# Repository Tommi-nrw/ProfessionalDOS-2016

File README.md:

Professional DOS was the fastest floppy speeder (excluding RAM disk setups)
for the Commodore 64 / 128 and 1541 / 1571 back in the '80s.
It was sold as RapiDOS in the US and DISK DEMON in the UK.

This is an upgraded version of the rebuilt Professional DOS from 2016.

The PCB works with both the 1541 and 1571. 
In the 1541, the board also lets you switch between Professional DOS, SpeedDOS, and DolphinDOS.

Version 1.42 (2026) eliminates the need for jumper wires.

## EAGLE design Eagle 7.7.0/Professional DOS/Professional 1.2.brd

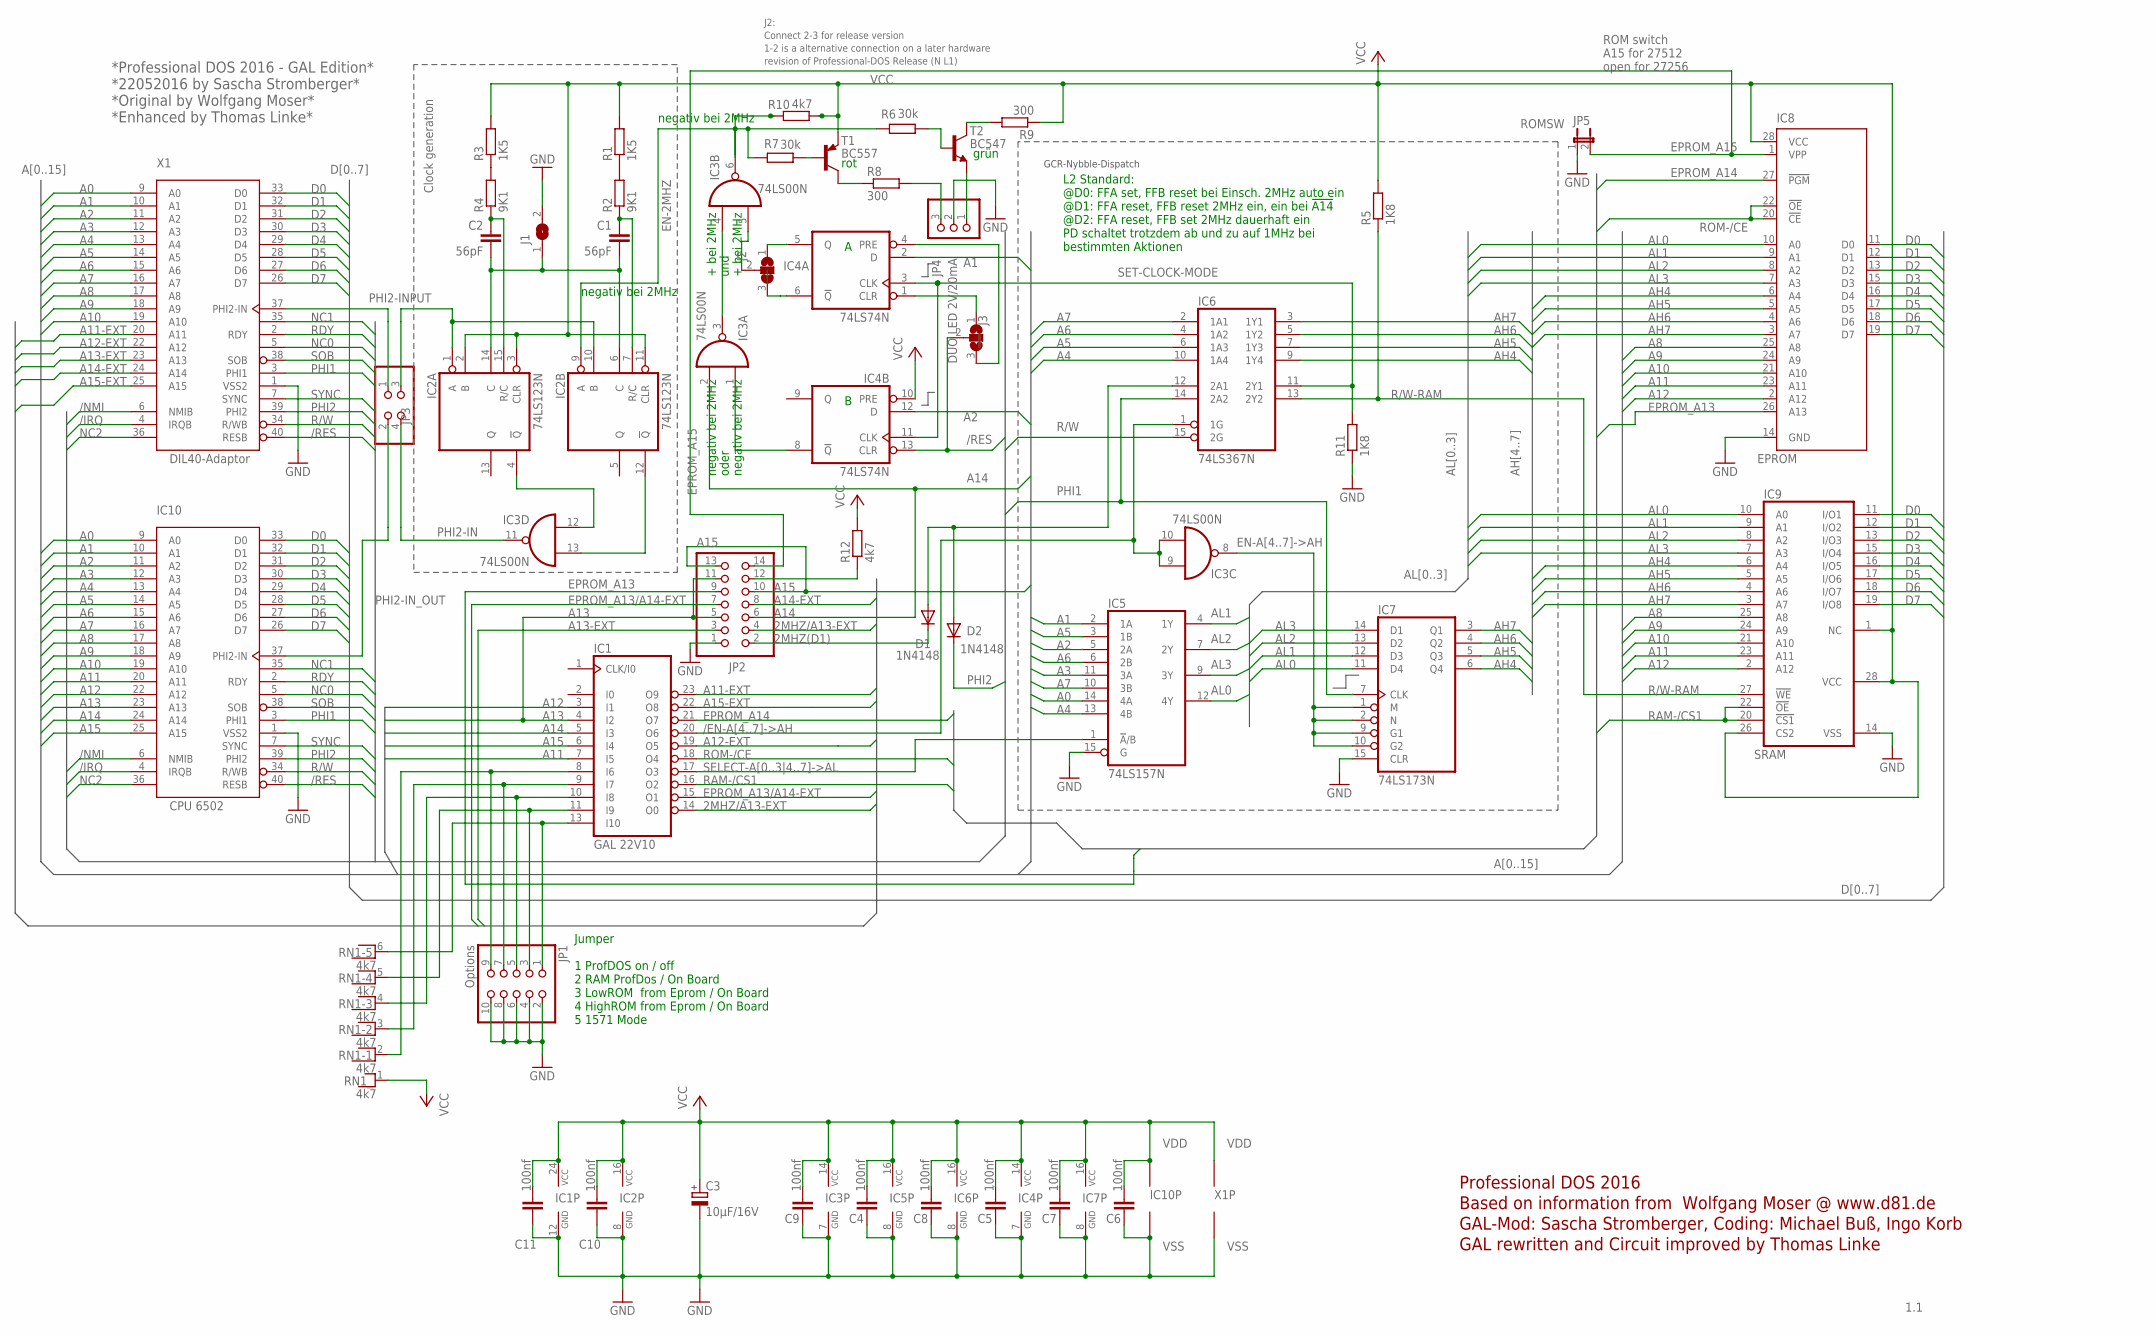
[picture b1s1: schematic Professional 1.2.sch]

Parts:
C1, C2: 56pF; C025-025X050
C3: 10µF/16V; TT2D4
C4, C5, C6, C7, C8, C9, C10, C11: 100nf; C2.5-2
D1, D2: 1N4148; D-5
IC1: GAL 22V10; DIL24-3
IC2: 74LS123N; DIL16
IC3: 74LS00N; DIL14
IC4: 74LS74N; DIL14
IC5: 74LS157N; DIL16
IC6: 74LS367N; DIL16
IC7: 74LS173N; DIL16
IC8: EPROM; DIL28-6
IC9: SRAM; DIL28-6
IC10: CPU 6502; DIL40
J1: 1; SJ
J2, J3: Alternativ connection for old version; SJ_2
JP1: Options; 2X05
JP2: 1; 2X07
JP3: 1; 2X02
JP4: DUO LED 2V/20mA; 1X03
JP5: ROMSW; JP1
R1, R3: 1K5; 0207/2V
R2, R4: 9K1; 0207/2V
R5, R11: 1K8; 0207/7
R6, R7: 30k; 0207/2V
R8, R9: 300; 0207/2V
R10: 4k7; 0207/2V
R12: 4k7; 0207/7
RN1: 4k7; RN-6
T1: BC557; TO92
T2: BC547; TO92
X1: DIL40-Adaptor; DIL40-BPLACE

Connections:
2MHZ(D1): D1.C, JP2.2
2MHZ/A13-EXT: IC1.14 (O0), JP2.4
/EN-A[4..7]->AH: IC1.20 (O6), IC3.9 (I0), IC3.10 (I1), IC6.1 (1G)
/IRQ: IC10.4 (IRQB), X1.4 (IRQB)
/NMI: IC10.6 (NMIB), X1.6 (NMIB)
/Q: IC4.6 (!Q), J2.3
/RES: IC4.13 (CLR), IC10.40 (RESB), J3.2, X1.40 (RESB)
A0: IC5.14 (4A), IC10.9 (A0), X1.9 (A0)
A1: IC4.2 (D), IC5.2 (1A), IC10.10 (A1), X1.10 (A1)
A2: IC4.12 (D), IC5.5 (2A), IC10.11 (A2), X1.11 (A2)
A3: IC5.11 (3A), IC10.12 (A3), X1.12 (A3)
A4: IC5.13 (4B), IC6.10 (1A4), IC10.13 (A4), X1.13 (A4)
A5: IC5.3 (1B), IC6.6 (1A3), IC10.14 (A5), X1.14 (A5)
A6: IC5.6 (2B), IC6.4 (1A2), IC10.15 (A6), X1.15 (A6)
A7: IC5.10 (3B), IC6.2 (1A1), IC10.16 (A7), X1.16 (A7)
A8: IC8.25 (A8), IC9.25 (A8), IC10.17 (A8), X1.17 (A8)
A9: IC8.24 (A9), IC9.24 (A9), IC10.18 (A9), X1.18 (A9)
A10: IC8.21 (A10), IC9.21 (A10), IC10.19 (A10), X1.19 (A10)
A11: IC1.7 (I5), IC8.23 (A11), IC9.23 (A11), IC10.20 (A11)
A11-EXT: IC1.23 (O9), X1.20 (A11)
A12: IC1.3 (I1), IC8.2 (A12), IC9.2 (A12), IC10.22 (A12)
A12-EXT: IC1.19 (O5), X1.22 (A12)
A13: IC1.4 (I2), IC10.23 (A13), JP2.5, JP2.11
A13-EXT: JP2.3, X1.23 (A13)
A14: IC1.5 (I3), IC3.2 (I1), IC10.24 (A14), JP2.6
A14-EXT: JP2.8, X1.24 (A14)
A15: IC1.6 (I4), IC10.25 (A15), JP2.10, JP2.13
A15-EXT: IC1.22 (O8), X1.25 (A15)
AH4: IC6.9 (1Y4), IC7.6 (Q4), IC8.6 (A4), IC9.6 (A4)
AH5: IC6.7 (1Y3), IC7.5 (Q3), IC8.5 (A5), IC9.5 (A5)
AH6: IC6.5 (1Y2), IC7.4 (Q2), IC8.4 (A6), IC9.4 (A6)
AH7: IC6.3 (1Y1), IC7.3 (Q1), IC8.3 (A7), IC9.3 (A7)
AL0: IC5.12 (4Y), IC7.11 (D4), IC8.10 (A0), IC9.10 (A0)
AL1: IC5.4 (1Y), IC7.12 (D3), IC8.9 (A1), IC9.9 (A1)
AL2: IC5.7 (2Y), IC7.13 (D2), IC8.8 (A2), IC9.8 (A2)
AL3: IC5.9 (3Y), IC7.14 (D1), IC8.7 (A3), IC9.7 (A3)
CLR: IC4.1 (CLR), J3.1
D0: IC8.11 (D0), IC9.11 (I/O1), IC10.33 (D0), X1.33 (D0)
D1: IC8.12 (D1), IC9.12 (I/O2), IC10.32 (D1), X1.32 (D1)
D2: IC8.13 (D2), IC9.13 (I/O3), IC10.31 (D2), X1.31 (D2)
D3: IC8.15 (D3), IC9.15 (I/O4), IC10.30 (D3), X1.30 (D3)
D4: IC8.16 (D4), IC9.16 (I/O5), IC10.29 (D4), X1.29 (D4)
D5: IC8.17 (D5), IC9.17 (I/O6), IC10.28 (D5), X1.28 (D5)
D6: IC8.18 (D6), IC9.18 (I/O7), IC10.27 (D6), X1.27 (D6)
D7: IC8.19 (D7), IC9.19 (I/O8), IC10.26 (D7), X1.26 (D7)
EN-2MHZ: IC2.9 (A), IC3.6 (O), R6.2, R7.1, R10.2
EN-A[4..7]->AH: IC3.8 (O), IC7.1 (M), IC7.2 (N), IC7.9 (G1), IC7.10 (G2)
EPROM_A13: IC8.26 (A13), JP2.9
EPROM_A13/A14-EXT: IC1.15 (O1), JP2.7
EPROM_A14: IC1.21 (O7), IC8.27 (!PGM)
EPROM_A15: IC8.1 (VPP), JP2.14, JP5.2
FETCH_CLOCK_MODE: D1.A, D2.A, IC6.12 (2A1)
GND: C3.-, C4.2, C5.2, C6.2, C7.2, C8.2, C9.2, C10.2, C11.2, IC1.12 (GND), IC2.8 (GND), IC3.7 (GND), IC4.7 (GND), IC5.8 (GND), IC5.15 (G), IC6.8 (GND), IC7.8 (GND), IC7.15 (CLR), IC8.14 (GND), IC9.14 (VSS), IC10.1 (VSS2), IC10.21 (VSS), J1.2, JP1.2, JP1.4, JP1.6, JP1.8, JP1.10, JP2.1, JP4.2, JP5.1, R11.1, X1.1 (VSS2), X1.21 (VSS)
unnamed: R3.1, R4.2
unnamed: C1.2, C2.2, IC2.6 (C), IC2.14 (C), J1.1
unnamed: C2.1, IC2.15 (R/C), R4.1
unnamed: C1.1, IC2.7 (R/C), R2.1
unnamed: R1.1, R2.2
unnamed: IC2.4 (!Q), IC3.12 (I0)
unnamed: R7.2, T1.2 (B)
unnamed: IC2.12 (!Q), IC3.13 (I1)
unnamed: IC3.5 (I1), J2.2
unnamed: R6.1, T2.2 (B)
unnamed: IC3.3 (O), IC3.4 (I0)
unnamed: IC3.1 (I0), IC4.8 (!Q)
unnamed: JP4.1, T2.1 (E)
unnamed: R9.2, T2.3 (C)
unnamed: JP4.3, R8.2
unnamed: R8.1, T1.3 (C)
NC0: IC10.5 (NC$3), X1.5 (NC$3)
NC1: IC10.35 (NC$1), X1.35 (NC$1)
NC2: IC10.36 (NC$2), X1.36 (NC$2)
ON-OFF: IC1.13 (I10), JP1.1, RN1.6
OPT2: IC1.11 (I9), JP1.3, RN1.5
OPT3: IC1.10 (I8), JP1.5, RN1.4
OPT4: IC1.9 (I7), JP1.7, RN1.3
OPT5: IC1.8 (I6), JP1.9, RN1.2
PHI1: IC6.14 (2A2), IC7.7 (CLK), IC10.3 (PHI1), X1.3 (PHI1)
PHI2: D2.C, IC10.39 (PHI2), X1.39 (PHI2)
PHI2-IN: IC3.11 (O), JP3.4
PHI2-INPUT: JP3.1, X1.37 (PHI2-IN)
PHI2-INPUT_OUT: IC2.1 (A), IC2.10 (B), JP3.3
PHI2-IN_OUT: IC10.37 (PHI2-IN), JP3.2
PRE: IC4.4 (PRE), J3.3
PULLUP: JP2.12, R12.1
Q: IC4.5 (Q), J2.1
R/W: IC6.15 (2G), IC10.34 (R/WB), X1.34 (R/WB)
R/W-RAM: IC6.13 (2Y2), IC9.27 (!WE), R5.1
RAM-/CS1: IC1.16 (O2), IC9.20 (!CS1), IC9.22 (!OE)
RDY: IC10.2 (RDY), X1.2 (RDY)
ROM-/CE: IC1.18 (O4), IC8.20 (!CE), IC8.22 (!OE)
SELECT-A[0..3|4..7]->AL: IC1.17 (O3), IC5.1 (!A!/B)
SET-CLOCK-MODE: IC4.3 (CLK), IC4.11 (CLK), IC6.11 (2Y1), R11.2
SOB: IC10.38 (SOB), X1.38 (SOB)
SYNC: IC10.7 (SYNC), X1.7 (SYNC)
VCC: C3.+, C4.1, C5.1, C6.1, C7.1, C8.1, C9.1, C10.1, C11.1, IC1.24 (VCC), IC2.2 (B), IC2.3 (CLR), IC2.11 (CLR), IC2.16 (VCC), IC3.14 (VCC), IC4.10 (PRE), IC4.14 (VCC), IC5.16 (VCC), IC6.16 (VCC), IC7.16 (VCC), IC8.28 (VCC), IC9.1 (NC), IC9.26 (CS2), IC9.28 (VCC), IC10.8 (VDD), R1.2, R3.2, R5.2, R9.1, R10.1, R12.2, RN1.1, T1.1 (E), X1.8 (VDD)

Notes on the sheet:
Clock generation
1.1
Professional DOS 2016 Based on information from Wolfgang Moser @ www.d81.de GAL-Mod: Sascha Stromberger, Coding: Michael Buß, Ingo Korb GAL rewritten and Circuit improved by Thomas Linke
*Professional DOS 2016 - GAL Edition* *22052016 by Sascha Stromberger* *Original by Wolfgang Moser* *Enhanced by Thomas Linke*
ROM switch A15 for 27512 open for 27256
1-2 is a alternative connection on a later hardware
revision of Professional-DOS Release (N L1)
GCR-Nybble-Dispatch
Connect 2-3 for release version
Jumper 1 ProfDOS on / off 2 RAM ProfDos / On Board 3 LowROM from Eprom / On Board 4 HighROM from Eprom / On Board 5 1571 Mode
rot
grün
J2:
L2 Standard: @D0: FFA set, FFB reset bei Einsch. 2MHz auto ein @D1: FFA reset, FFB reset 2MHz ein, ein bei !A14 @D2: FFA reset, FFB set 2MHz dauerhaft ein PD schaltet trotzdem ab und zu auf 1MHz bei bestimmten Aktionen
negativ bei 2MHz
+ bei 2MHz
oder
und

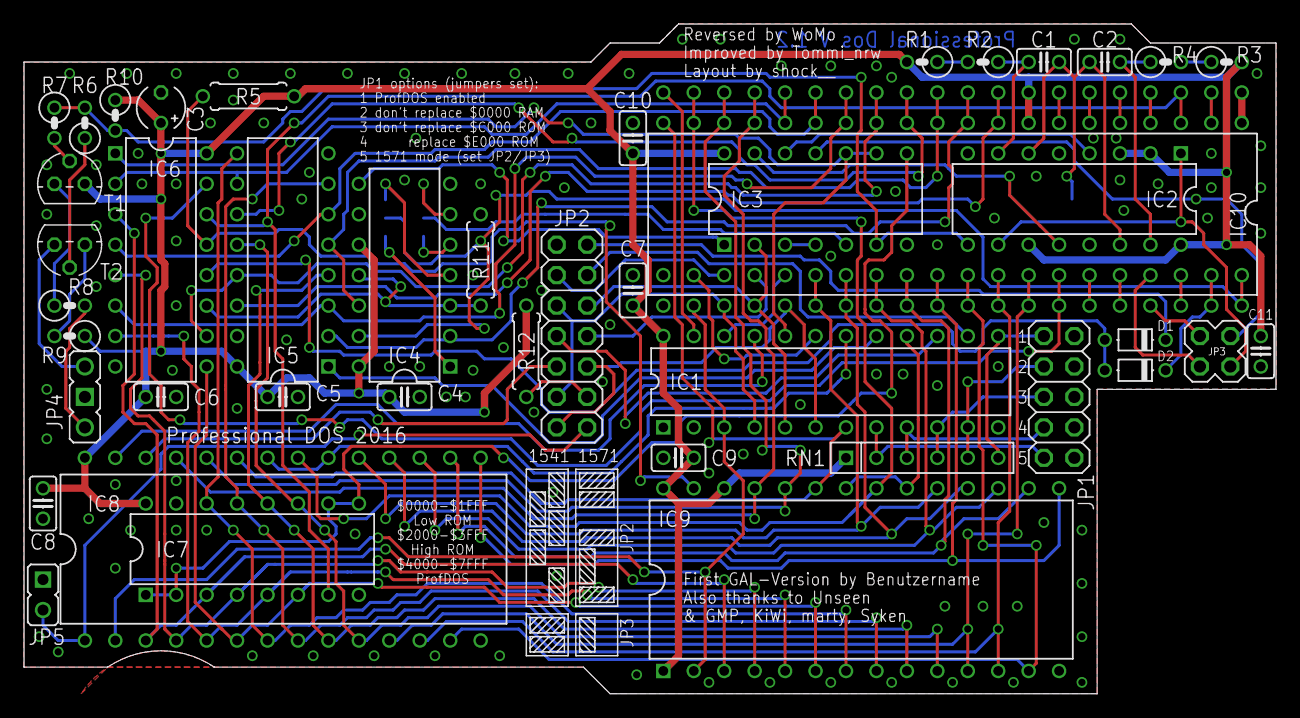
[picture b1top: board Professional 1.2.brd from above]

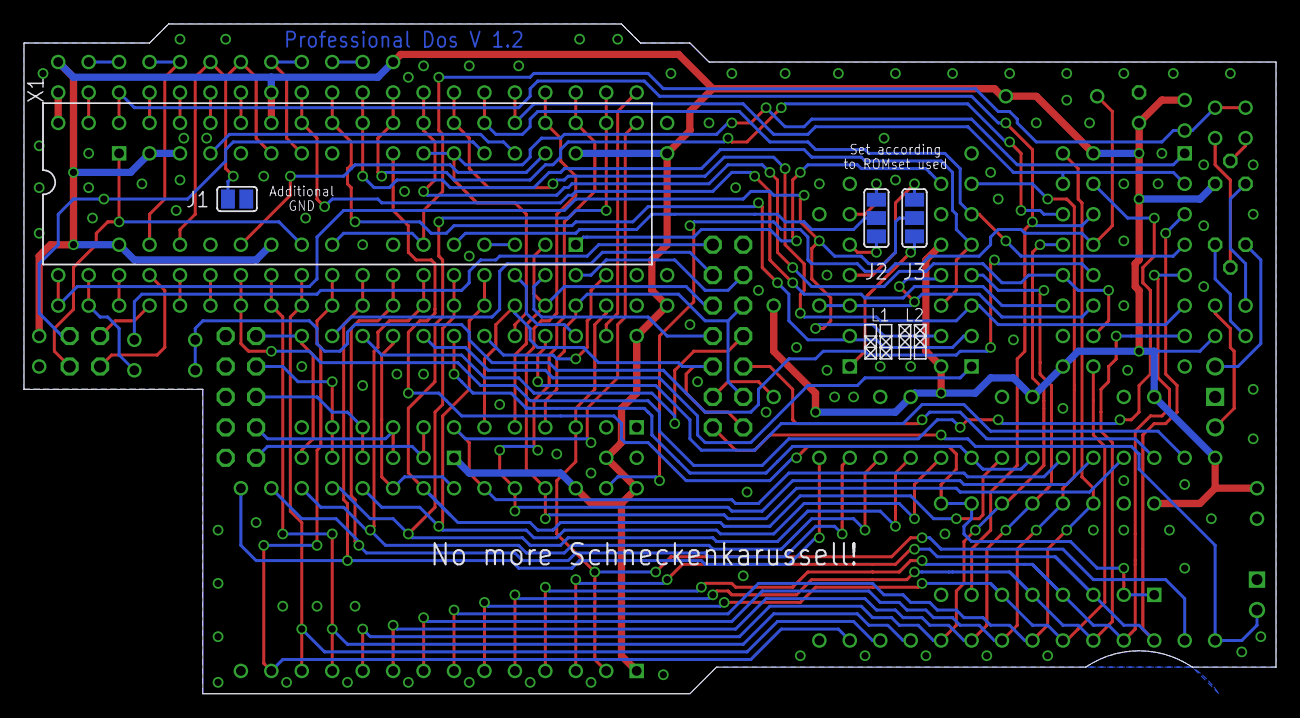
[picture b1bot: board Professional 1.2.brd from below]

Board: 2 copper layers, 104.5 x 55.9 mm, 47 parts (3 on the bottom side), 96 nets.

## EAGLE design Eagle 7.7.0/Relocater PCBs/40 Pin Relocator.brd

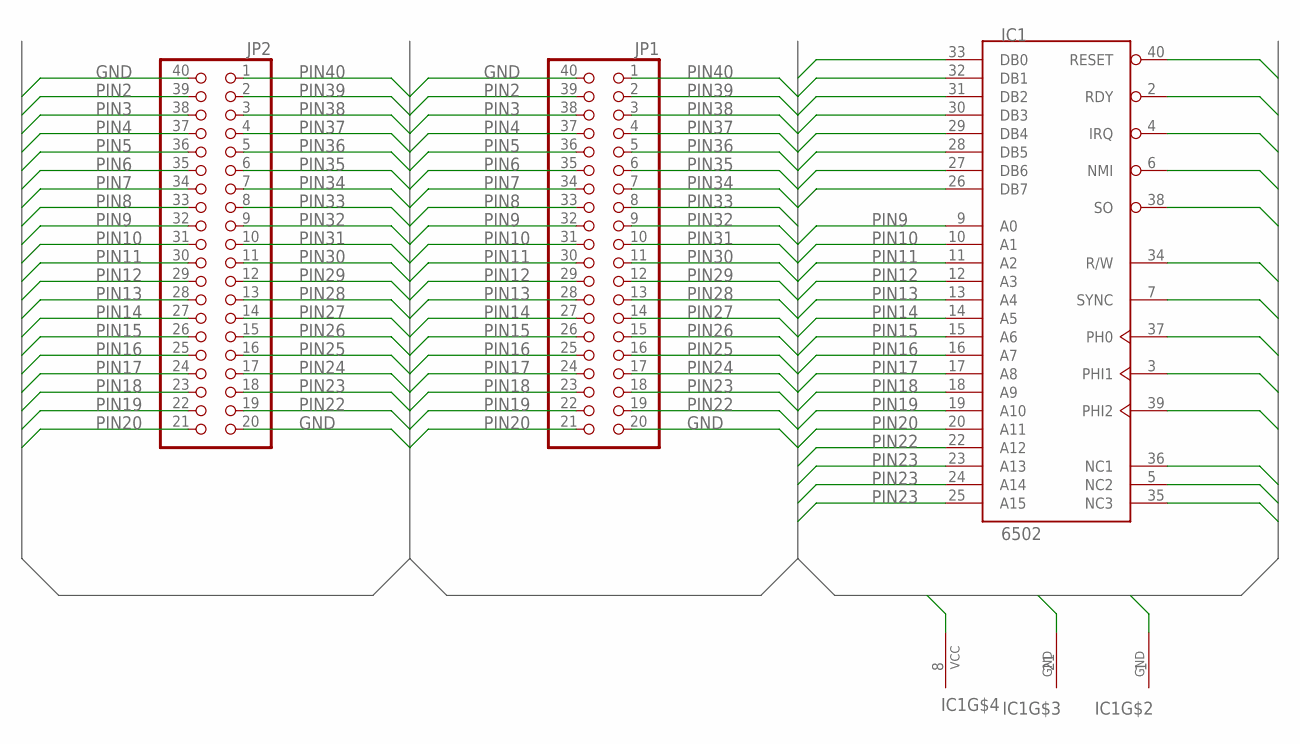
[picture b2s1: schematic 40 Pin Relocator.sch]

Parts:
IC1: 6502; DIP40
JP1, JP2: PINHD-2X20; 2X20

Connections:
GND: IC1.1 (GND), IC1.21 (GND), JP1.20 (39), JP1.40 (2), JP2.20 (39), JP2.40 (2)
PIN2: IC1.2 (RDY), JP1.39 (4), JP2.39 (4)
PIN3: IC1.3 (PHI1), JP1.38 (6), JP2.38 (6)
PIN4: IC1.4 (IRQ), JP1.37 (8), JP2.37 (8)
PIN5: IC1.5 (NC2), JP1.36 (10), JP2.36 (10)
PIN6: IC1.6 (NMI), JP1.35 (12), JP2.35 (12)
PIN7: IC1.7 (SYNC), JP1.34 (14), JP2.34 (14)
PIN8: IC1.8 (VCC), JP1.33 (16), JP2.33 (16)
PIN9: IC1.9 (A0), JP1.32 (18), JP2.32 (18)
PIN10: IC1.10 (A1), JP1.31 (20), JP2.31 (20)
PIN11: IC1.11 (A2), JP1.30 (22), JP2.30 (22)
PIN12: IC1.12 (A3), JP1.29 (24), JP2.29 (24)
PIN13: IC1.13 (A4), JP1.28 (26), JP2.28 (26)
PIN14: IC1.14 (A5), JP1.27 (28), JP2.27 (28)
PIN15: IC1.15 (A6), JP1.26 (30), JP2.26 (30)
PIN16: IC1.16 (A7), JP1.25 (32), JP2.25 (32)
PIN17: IC1.17 (A8), JP1.24 (34), JP2.24 (34)
PIN18: IC1.18 (A9), JP1.23 (36), JP2.23 (36)
PIN19: IC1.19 (A10), JP1.22 (38), JP2.22 (38)
PIN20: IC1.20 (A11), JP1.21 (40), JP2.21 (40)
PIN22: IC1.22 (A12), JP1.19 (37), JP2.19 (37)
PIN23: IC1.23 (A13), JP1.18 (35), JP2.18 (35)
PIN24: IC1.24 (A14), JP1.17 (33), JP2.17 (33)
PIN25: IC1.25 (A15), JP1.16 (31), JP2.16 (31)
PIN26: IC1.26 (DB7), JP1.15 (29), JP2.15 (29)
PIN27: IC1.27 (DB6), JP1.14 (27), JP2.14 (27)
PIN28: IC1.28 (DB5), JP1.13 (25), JP2.13 (25)
PIN29: IC1.29 (DB4), JP1.12 (23), JP2.12 (23)
PIN30: IC1.30 (DB3), JP1.11 (21), JP2.11 (21)
PIN31: IC1.31 (DB2), JP1.10 (19), JP2.10 (19)
PIN32: IC1.32 (DB1), JP1.9 (17), JP2.9 (17)
PIN33: IC1.33 (DB0), JP1.8 (15), JP2.8 (15)
PIN34: IC1.34 (R/W), JP1.7 (13), JP2.7 (13)
PIN35: IC1.35 (NC3), JP1.6 (11), JP2.6 (11)
PIN36: IC1.36 (NC1), JP1.5 (9), JP2.5 (9)
PIN37: IC1.37 (PH0), JP1.4 (7), JP2.4 (7)
PIN38: IC1.38 (SO), JP1.3 (5), JP2.3 (5)
PIN39: IC1.39 (PHI2), JP1.2 (3), JP2.2 (3)
PIN40: IC1.40 (RESET), JP1.1, JP2.1

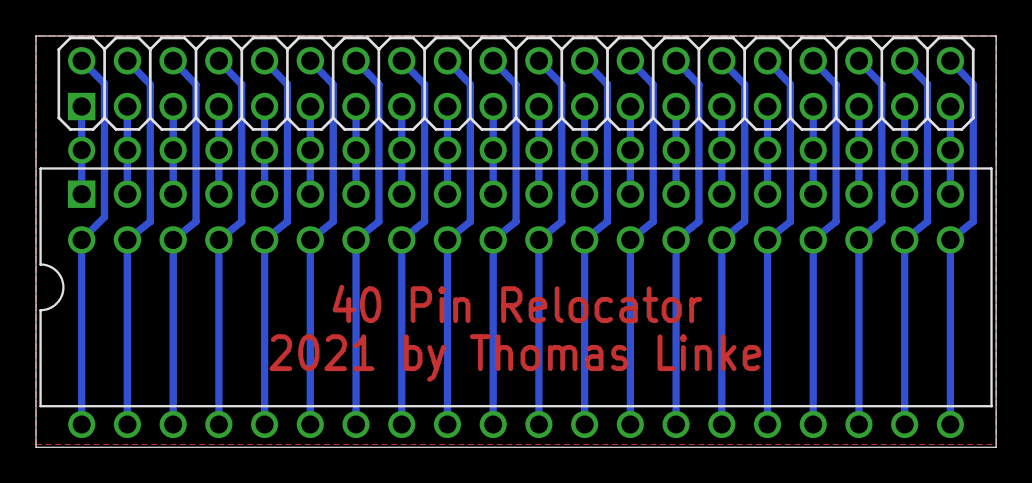
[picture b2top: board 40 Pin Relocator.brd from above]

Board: 2 copper layers, 53.3 x 22.8 mm, 3 parts (1 on the bottom side), 39 nets.
